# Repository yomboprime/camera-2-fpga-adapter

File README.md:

# camera-2-fpga-adapter
Breakout board adapter for Camera with digital interface (OV5462, OV7670...) to Lattice HX8K FPGA board.

Made with Kicad.

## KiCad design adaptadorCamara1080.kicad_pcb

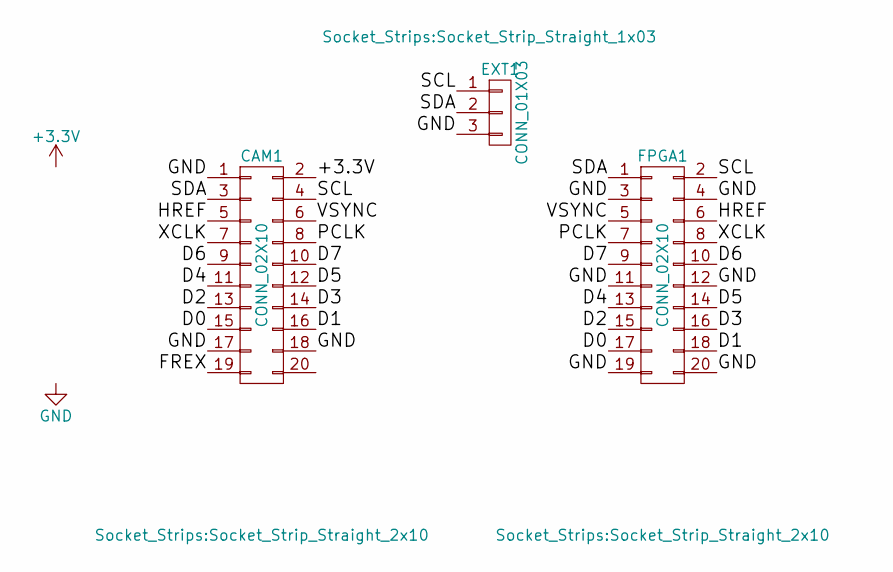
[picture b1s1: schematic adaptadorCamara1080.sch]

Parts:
CAM1: CONN_02X10; Socket_Strip_Straight_2x10
EXT1: CONN_01X03; Socket_Strip_Straight_1x03
FPGA1: CONN_02X10; Socket_Strip_Straight_2x10

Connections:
/+3.3V: CAM1.2
/D0: CAM1.15, FPGA1.17
/D1: CAM1.16, FPGA1.18
/D2: CAM1.13, FPGA1.15
/D3: CAM1.14, FPGA1.16
/D4: CAM1.11, FPGA1.13
/D5: CAM1.12, FPGA1.14
/D6: CAM1.9, FPGA1.10
/D7: CAM1.10, FPGA1.9
/FREX: CAM1.19
/HREF: CAM1.5, FPGA1.6
/PCLK: CAM1.8, FPGA1.7
/SCL: CAM1.4, EXT1.1, FPGA1.2
/SDA: CAM1.3, EXT1.2, FPGA1.1
/VSYNC: CAM1.6, FPGA1.5
/XCLK: CAM1.7, FPGA1.8
GND: CAM1.1, CAM1.17, CAM1.18, EXT1.3, FPGA1.3, FPGA1.4, FPGA1.11, FPGA1.12, FPGA1.19, FPGA1.20

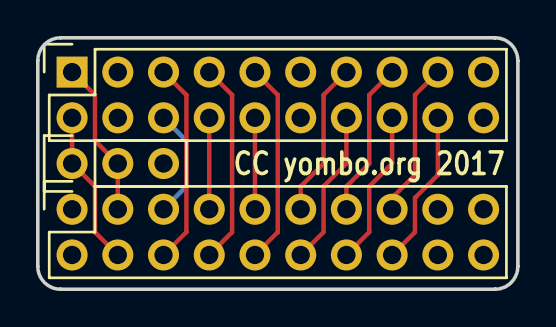
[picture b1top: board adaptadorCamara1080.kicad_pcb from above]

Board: 2 copper layers, 26.7 x 14.0 mm, 3 parts (0 on the bottom side), 15 nets.

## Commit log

2017-11-23 Change readme
